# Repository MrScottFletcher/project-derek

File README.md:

# Derek Halloween Animatronic Eyes in a Can System

This repository is for the Derek Halloween Animatronic Eyes in a Can System: a distributed animatronic display built around clusters of moving eyeballs housed in tin cans. The system is designed for synchronized motion, lighting, sound, motion detection, and show control across multiple wireless nodes.

## Project Overview

Each pair of animatronic eyes in a can is called a `Derrick`. A single cluster can control up to eight Derricks, and the full installation can scale to up to 15 cluster nodes coordinated by one Master Control Unit (`MCU`).

Each Derrick includes:

- Two servos
- Addressable RGB LED illumination
- Independent participation in animations and show sequences

The two servos are used for:

- Horizontal eye direction
- Vertical eye lift and conceal/reveal motion

The vertical servo not only raises and lowers the eyes, but also lifts the can lid as the eyes emerge.

## System Architecture

The system is split into two primary firmware roles:

- `MCU` (Master Control Unit)
- `Cluster` controllers

### Master Control Unit

The MCU is the orchestration layer. Its responsibilities include:

- Running or integrating with QLC+ for show control
- Converting OSC-based control intent into cluster commands
- Managing configuration and persistent settings
- Providing a web UI for setup, control, and manual triggering
- Coordinating performances across one or more clusters
- Receiving status updates and PIR motion events from clusters

### Cluster Controllers

Each cluster controller is responsible for local hardware control and fail-safe behavior. A cluster manages:

- Up to eight Derricks
- Servo motion control through a PWM servo controller
- Addressable RGB LED segments for each Derrick
- Two DFPlayer MP3 audio modules
- Audio amplifiers and speakers
- Three PIR motion sensors: left, center, and right
- Wireless communication back to the MCU via ESP-NOW

Clusters should continue operating gracefully even if some hardware subsystems are unavailable, and they should report status back to the MCU whenever possible.

## Control and Communication

The system uses:

- `ESP32`-class controllers
- `ESP-NOW` for wireless MCU-to-cluster communication
- `OSC` and `QLC+` as part of the higher-level control workflow

Communication is bi-directional:

- The MCU sends orchestration, animation, lighting, audio, and motion commands to clusters
- Clusters report status and PIR sensor activity back to the MCU

Wireless message formats should be treated as stable contracts between the MCU and cluster firmware.

## Motion, Lighting, and Audio

### Motion

Each Derrick has:

- One servo for left/right aiming
- One servo for up/down lift and conceal/reveal

Expected motion behavior:

- Straight ahead is centered
- Horizontal movement can sweep left or right within configured limits
- Vertical motion can hide the eyes inside the can or raise them fully into view
- Calibration should support placement of each Derrick within a 360-degree installation layout

Motion control is safety-sensitive and should remain deterministic, non-blocking, and range-clamped.

### Lighting

Each cluster includes addressable RGB LED segments connected in series, with each Derrick owning its own lighting section. Lighting can be used to:

- Illuminate the eyes
- Set mood and scene color
- Synchronize with movement and sound cues

### Audio

Each cluster includes two DFPlayer units, each with an SD card containing an identical numbered MP3 library. Audio can be:

- Triggered per Derrick action
- Triggered by multi-Derrick animations
- Run independently per cluster
- Coordinated across multiple clusters

## Sensing and Reactive Behavior

Each cluster includes three PIR sensors:

- Left
- Center
- Right

These sensors provide motion events that can be sent back to the MCU and used by QLC+ or other orchestration logic to:

- Trigger performances
- Redirect gaze toward detected motion
- Start random or interactive animation sequences

The long-term design also allows for more precise tracking input based on a 360-degree position around the installation.

## Performances and Configuration

The system is intended to support named performances that can span:

- A single Derrick
- A single cluster
- Multiple clusters
- The entire installation

Configurable system concerns include:

- Number of clusters in the installation
- Number of Derricks present in each cluster
- Calibration for each Derrick's motion range and aiming
- Persistent MCU-side settings for orchestration and control

Triggers for performances may include:

- Random timing
- PIR motion input
- Manual operator control through the MCU web interface

## Planned Repository Structure

The repository is expected to organize code by deployable target:

```text
project-derek/
  derek-cluster/
    src/
  derek-mcu/
    src/
```

In this structure:

- `derek-cluster/src/` contains cluster firmware and direct hardware control logic
- `derek-mcu/src/` contains master orchestration, configuration, communications, and web UI logic

## Engineering Guidelines

This project follows a few important design principles:

- Keep MCU and cluster responsibilities clearly separated
- Prefer deterministic, non-blocking runtime behavior
- Avoid changing hardware mappings unless explicitly required
- Preserve graceful degradation when hardware components are unavailable
- Use named constants and configuration structures rather than scattered magic numbers
- Keep serial logging concise and easy to disable
- Make persistent-setting defaults explicit and safe

For embedded code, motion, LEDs, audio, radio, and sensing should be able to operate concurrently without blocking the control loop.

## Development Notes

General project commands:

- Install: `npm install`
- Development: `npm run dev`
- Test: `npm test`
- Lint: `npm run lint`

Additional implementation details may vary between the MCU application and the cluster firmware as those directories are added.

## Current Status

This repository is currently in an early stage and serves as the home for the Derek system architecture, firmware organization, and future control software.

As the codebase grows, this README should be expanded with:

- Build instructions per target
- Hardware BOM and wiring references
- Wireless protocol details
- Calibration workflow
- Performance authoring and deployment notes

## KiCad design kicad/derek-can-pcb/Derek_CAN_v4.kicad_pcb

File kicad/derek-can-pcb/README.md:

# Derek CAN Interface Board Rev 4

This revision adds a schematic and corrects the LED-return net mismatch found in Rev 3.

## Authoritative RJ45 pinout

1. +5 V
2. +5 V
3. GND
4. GND
5. PAN_PWM
6. LIFT_PWM
7. LED_FROM_CLUSTER
8. LED_RETURN_CLUSTER

This is **not Ethernet**. It is intended only for a straight-through 8P8C patch cable connected to the matching Cluster Controller port.

## Components

- C1: 1000 uF, 16 V, radial aluminum electrolytic, 105 C, 5.0 mm lead spacing
- C2: 100 nF, 50 V, X7R radial ceramic, 2.5 mm lead spacing
- R1: 330 ohm axial through-hole resistor

## Schematic format

`Derek_CAN_v4.sch` is a KiCad legacy schematic. Current KiCad versions should open it and offer to convert/save it as `Derek_CAN_v4.kicad_sch`. This was chosen because the legacy format is compact and less prone to hand-generated parser errors.

## Important correction from Rev 3

J5 pin 1 (data from the final LED) and J1 pin 8 (return to the cluster) now share the same net: `LED_RETURN_CLUSTER`.

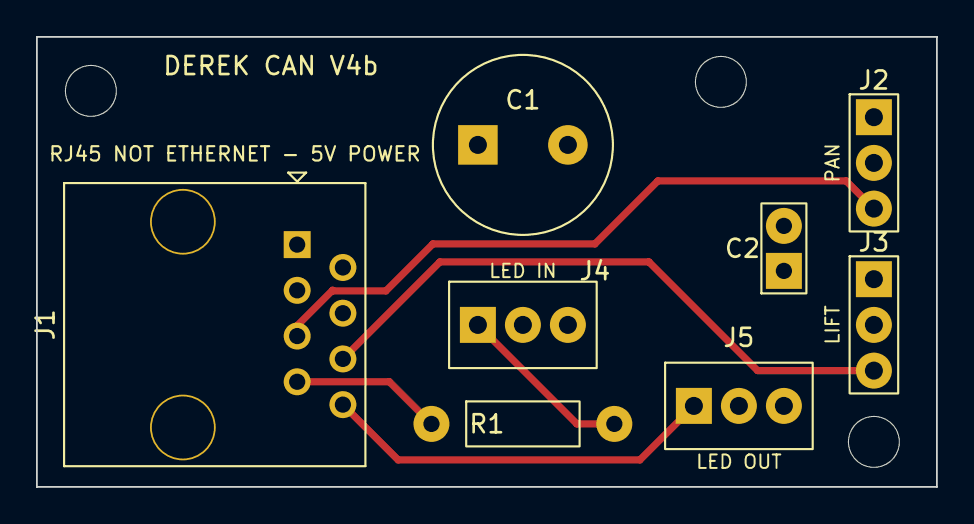
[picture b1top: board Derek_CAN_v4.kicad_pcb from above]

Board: 4 copper layers, 50.0 x 25.0 mm, 8 parts (0 on the bottom side), 7 nets.

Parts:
C1: 1000uF 16V; CP_Radial_D10.0mm_P5.00mm
C2: 100nF 50V X7R; C_Disc_D5.0mm_W2.5mm_P2.50mm
J1: FMHXG_RJ45NMCCFC; RJ45_OST_PJ012-8P8CX_Vertical
J2: PAN_SERVO; PinHeader_1x03_P2.54mm_Vertical
J3: LIFT_SERVO; PinHeader_1x03_P2.54mm_Vertical
J4, J5: JST-XH-3; JST_XH_B3B-XH-A_1x03_P2.50mm_Vertical
R1: 330R; R_Axial_DIN0207_L6.3mm_D2.5mm_P10.16mm_Horizontal

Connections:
5V: C1.1 (+), C2.1, J1.1, J1.2, J2.2 (+5V), J3.2 (+5V), J4.2 (+5V), J5.2 (+5V)
GND: C1.2 (-), C2.2, J1.3, J1.4, J2.1 (GND), J3.1 (GND), J4.3 (GND), J5.3 (GND)
LED_FROM_CLUSTER: J1.7, R1.1
LED_RETURN_CLUSTER: J1.8, J5.1 (DATA)
LED_TO_FIRST: J4.1 (DATA), R1.2
LIFT_PWM: J1.6, J3.3 (SIGNAL)
PAN_PWM: J1.5, J2.3 (SIGNAL)

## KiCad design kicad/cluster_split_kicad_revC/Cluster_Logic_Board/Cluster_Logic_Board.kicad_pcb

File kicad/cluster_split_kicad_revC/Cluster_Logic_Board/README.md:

# Cluster Logic Board Rev G — U1 rebuilt

This revision starts over on U1 rather than translating the bare ESP32-S3 MCU symbol.

## Why this fixes the prior problem

U1 now uses **physical development-board header identifiers** as both schematic pin numbers and PCB pad numbers:

- `J1.1` through `J1.22` = left header
- `J3.1` through `J3.22` = right header

This makes it impossible for KiCad to confuse a DevKit physical header position with a bare ESP32-S3 package pin number.

Key power connections:
- U1 `J1.1` and `J1.2` = 3V3 -> `+3V3_LOGIC`
- U1 `J1.21` = 5V -> `+5V_LOGIC`
- U1 `J1.22`, `J3.1`, `J3.21`, `J3.22` = GND -> `GND`

## GPIO assignments

- GPIO4 = ID0
- GPIO5 = ID1
- GPIO6 = ID2
- GPIO7 = ID3
- GPIO8 = I2C SDA
- GPIO9 = I2C SCL
- GPIO10 = LED data
- GPIO11 = PIR left
- GPIO12 = PIR center
- GPIO13 = PIR right
- GPIO14 = PCA9685 OE
- GPIO15 = ESP TX to DFPlayer #2 RX via R6
- GPIO16 = ESP RX from DFPlayer #2 TX
- GPIO17 = ESP TX to DFPlayer #1 RX via R5
- GPIO18 = ESP RX from DFPlayer #1 TX

## Pins intentionally avoided

- GPIO0, GPIO3, GPIO45, GPIO46: boot/strapping-related
- GPIO19, GPIO20: native USB D-/D+
- GPIO35, GPIO36, GPIO37: avoided for N16R8 / octal PSRAM compatibility
- GPIO43, GPIO44: left free for UART0/programming/debug convenience

## J10 — NOT CHANGED

1. GND
2. GND
3. +3V3_LOGIC
4. I2C_SDA
5. I2C_SCL
6. LED_DATA_3V3
7. PCA_OE_N
8. SPARE

The Cluster Servo Board is not changed by this package.

## Included verification aids

- `U1_Hosyond_Pin_Assignment_Audit.csv`
- `ESP32_Pin_Assignments.h`
- custom U1 footprint under `Halloween.pretty`

Open `Cluster_Logic_Board.kicad_pro` as a KiCad project, then use Update PCB from Schematic. Refill zones and run ERC/DRC before fabrication.

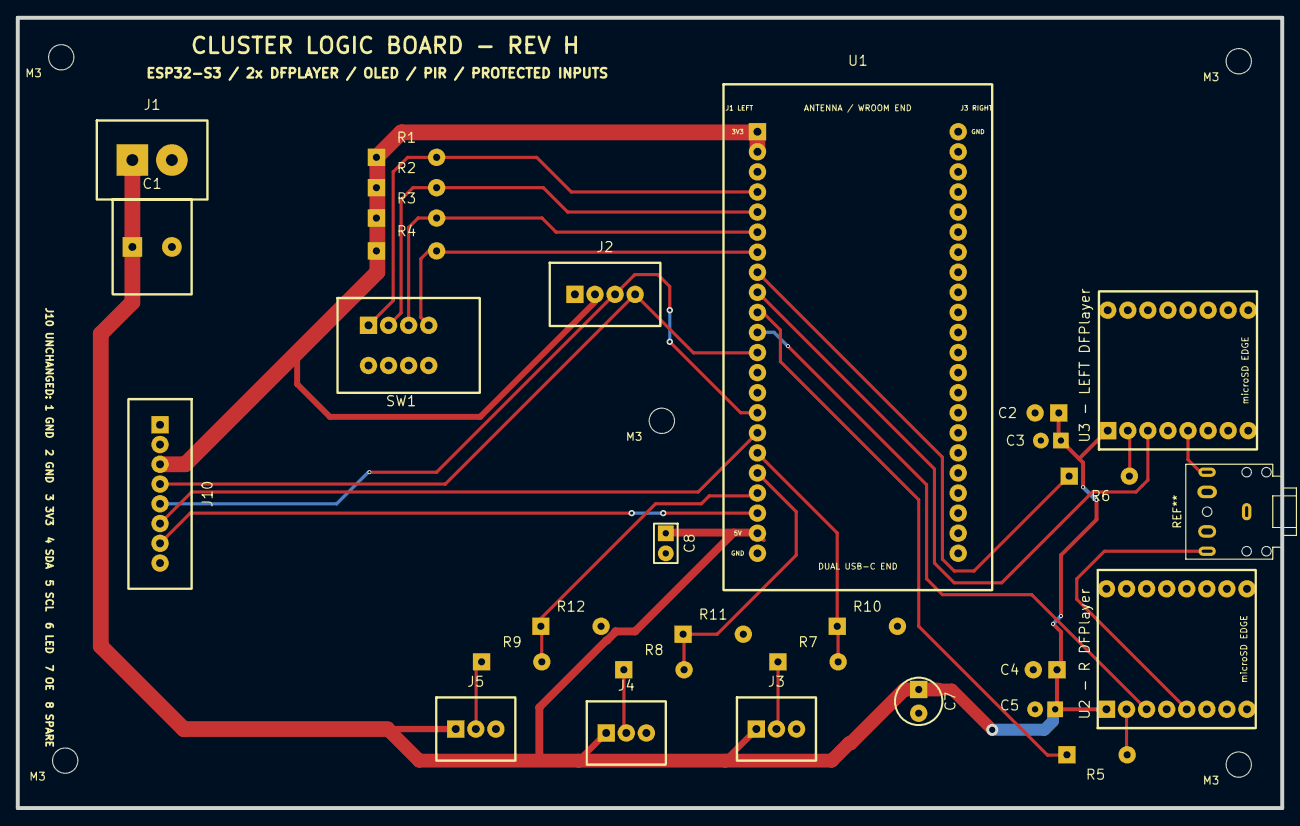
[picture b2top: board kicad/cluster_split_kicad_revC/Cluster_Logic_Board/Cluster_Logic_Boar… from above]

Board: 2 copper layers, 160.0 x 100.0 mm, 34 parts (0 on the bottom side), 23 nets.

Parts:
C1: 1000uF_10V
C2, C4: 47uF 10V; C_Radial_47uF
C3, C5: 100nF; C_Ceramic_100nF
C7: 47uF 10V ESP32; C_Radial_47uF
C8: 100nF ESP32; C_Ceramic_100nF
J1: POWER_5V
J2: OLED_1x4
J3: PIR_LEFT
J4: PIR_CENTER
J5: PIR_RIGHT
J10: JST_XH_8
M3, M3#2, M3#3, M3#4, M3#5: MountingHole_3.2mm_M3
R1, R2, R3, R4: 10k; R_Axial_10k
R5: 1k DF1 RX; R_Axial_1k
R6: 1k DF2 RX; R_Axial_1k
R7: 1k PIR L; R_Axial_1k
R8: 1k PIR C; R_Axial_1k
R9: 1k PIR R; R_Axial_1k
R10, R11, R12: 100k; R_Axial_100k
SW1: DIPSW_4
U1: Hosyond ESP32-S3 N16R8 44-pin DevKit; Hosyond_ESP32-S3_N16R8_44P
U2 - R DFPlayer, U3 - LEFT DFPlayer: WWZMDiB DFPlayer Mini; DFPlayer_Mini_16P

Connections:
+3V3_LOGIC: J2.2, J10.3, R1.1, R2.1, R3.1, R4.1, U1.J1.1, U1.J1.2
+5V_LOGIC: C1.1, C2.1, C3.1, C4.1, C5.1, C7.1, C8.1, J1.1, J3.1, J4.1, J5.1, U1.J1.21, U2 - R DFPlayer.1, U3 - LEFT DFPlayer.1
DF1_RX: R5.2, U2 - R DFPlayer.2
DF1_RX_ESP: R5.1, U1.J1.10
DF1_TX: U1.J1.11, U2 - R DFPlayer.3
DF2_RX: R6.2, U3 - LEFT DFPlayer.2
DF2_RX_ESP: R6.1, U1.J1.8
DF2_TX: U1.J1.9, U3 - LEFT DFPlayer.3
GND: C1.2, C2.2, C3.2, C4.2, C5.2, C7.2, C8.2, J1.2, J2.1, J3.3, J4.3, J5.3, J10.1, J10.2, R10.2, R11.2, R12.2, SW1.5, SW1.6, SW1.7, SW1.8, U1.J1.22, U1.J3.1, U1.J3.21, U1.J3.22, U2 - R DFPlayer.7, U2 - R DFPlayer.10, U3 - LEFT DFPlayer.7, U3 - LEFT DFPlayer.10
I2C_SCL: J2.3, J10.5, U1.J1.15
I2C_SDA: J2.4, J10.4, U1.J1.12
ID0: R1.2, SW1.1, U1.J1.4
ID1: R2.2, SW1.2, U1.J1.5
ID2: R3.2, SW1.3, U1.J1.6
ID3: R4.2, SW1.4, U1.J1.7
LED_DATA_3V3: J10.6, U1.J1.16
PCA_OE_N: J10.7, U1.J1.20
PIR_CENTER: R8.2, R11.1, U1.J1.18
PIR_CENTER_CONN: J4.2, R8.1
PIR_LEFT: R7.2, R10.1, U1.J1.17
PIR_LEFT_CONN: J3.2, R7.1
PIR_RIGHT: R9.2, R12.1, U1.J1.19
PIR_RIGHT_CONN: J5.2, R9.1

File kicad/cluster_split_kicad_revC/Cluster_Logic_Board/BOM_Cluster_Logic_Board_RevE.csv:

Reference,Qty,Part / Value,Footprint,Assembly,Purpose / placement
U1,1,Hosyond ESP32-S3 N16R8 Dev Board,Existing 2x22 carrier footprint,Hand,Controller module
"U2,U3",2,WWZMDiB DFPlayer Mini compatible,Halloween:DFPlayer_Mini_16P,Hand,Audio modules
J2,1,"0.96in SSD1306 I2C OLED, GND/VCC/SCL/SDA",Halloween:OLED_SSD1306_096_4P,Hand,Display
"J3,J4,J5",3,PIR 3-pin headers,2.54mm THT,Hand,PIR sensors
SW1,1,4-position DIP switch,DIP-8 W7.62mm,Hand,Cluster ID
J10,1,JST-XH 1x8 2.50mm,JST_XH_B8B-XH-A,Hand,UNCHANGED servo-board interconnect
R1-R4,4,10k 1/4W axial,DIN0207 axial THT,Hand,SW1 ID pull-ups to 3.3V
R5-R6,2,1k 1/4W axial,DIN0207 axial THT,Hand,ESP32 TX -> DFPlayer RX
R7-R9,3,1k 1/4W axial,DIN0207 axial THT,Hand,PIR signal series protection
R10-R12,3,100k 1/4W axial,DIN0207 axial THT,Hand,PIR input pulldowns
C1,1,1000uF 10V radial electrolytic,CP_Radial_D10mm_P5mm,Hand,Main logic-board bulk at J1
"C2,C4",2,47uF 10V radial electrolytic,CP_Radial_D5mm_P2mm,Hand,One near each DFPlayer
"C3,C5",2,100nF ceramic,C_Disc_D5mm_P5mm,Hand,One near each DFPlayer
C6,1,100nF ceramic,C_Disc_D5mm_P5mm,Hand,PIR connector-bank bypass
C7,1,47uF 10V radial electrolytic,CP_Radial_D5mm_P2mm,Hand,Local bulk near ESP32 5V/VIN
C8,1,100nF ceramic,C_Disc_D5mm_P5mm,Hand,Local high-frequency bypass near ESP32 5V/VIN

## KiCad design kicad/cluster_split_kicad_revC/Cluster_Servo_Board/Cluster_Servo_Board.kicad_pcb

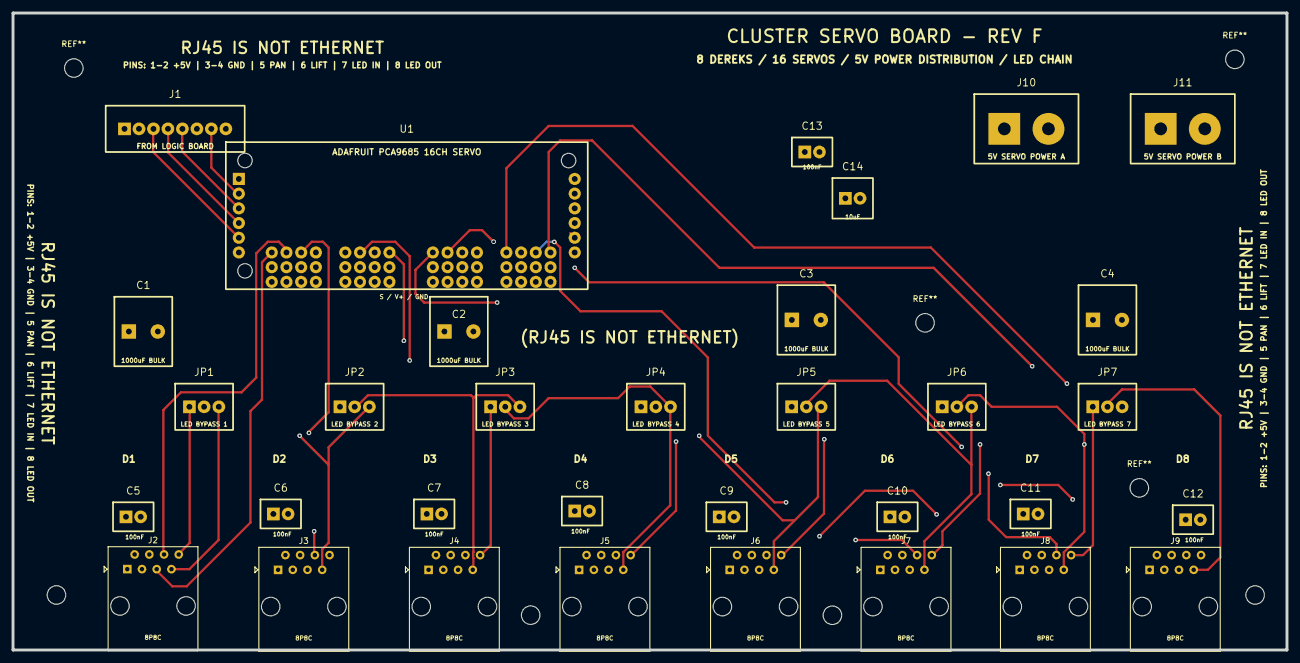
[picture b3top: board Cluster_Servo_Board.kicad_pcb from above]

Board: 4 copper layers, 220.0 x 110.0 mm, 33 parts (0 on the bottom side), 37 nets.

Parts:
C1, C2, C3, C4: 1000uF_10V
C5, C6, C7, C8, C9, C10, C11, C12, C13: 100nF
C14: 10uF
J1: JST_XH_8
J2, J3, J4, J5, J6, J7, J8, J9: RJ45_Amphenol_54602-x08_Horizontal
J10, J11: POWER_5V_HICUR
JP1, JP2, JP3, JP4, JP5, JP6, JP7: LED_BYPASS
U1: ADAFRUIT_PCA9685_16CH_PRODUCT_815; Adafruit_PCA9685_16CH_Product815_Carrier

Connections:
+3V3_LOGIC: J1.3, U1.L5, U1.R5
+5V_SERVO: C1.1, C2.1, C3.1, C4.1, C5.1, C6.1, C7.1, C8.1, C9.1, C10.1, C11.1, C12.1, C13.1, C14.1, J2.1, J2.2, J3.1, J3.2, J4.1, J4.2, J5.1, J5.2, J6.1, J6.2, J7.1, J7.2, J8.1, J8.2, J9.1, J9.2, J10.1, J11.1, U1.L6, U1.R6, U1.V0, U1.V1, U1.V2, U1.V3, U1.V4, U1.V5, U1.V6, U1.V7, U1.V8, U1.V9, U1.V10, U1.V11, U1.V12, U1.V13, U1.V14, U1.V15
GND: C1.2, C2.2, C3.2, C4.2, C5.2, C6.2, C7.2, C8.2, C9.2, C10.2, C11.2, C12.2, C13.2, C14.2, J1.1, J1.2, J2.3, J2.4, J3.3, J3.4, J4.3, J4.4, J5.3, J5.4, J6.3, J6.4, J7.3, J7.4, J8.3, J8.4, J9.3, J9.4, J10.2, J11.2, U1.G0, U1.G1, U1.G2, U1.G3, U1.G4, U1.G5, U1.G6, U1.G7, U1.G8, U1.G9, U1.G10, U1.G11, U1.G12, U1.G13, U1.G14, U1.G15, U1.L1, U1.R1
I2C_SCL: J1.5, U1.L3, U1.R3
I2C_SDA: J1.4, U1.L4, U1.R4
LED_IN1: J2.7, JP1.3
LED_IN2: J3.7, JP1.2, JP2.3
LED_IN3: J4.7, JP2.2, JP3.3
LED_IN4: J5.7, JP3.2, JP4.3
LED_IN5: J6.7, JP4.2, JP5.3
LED_IN6: J7.7, JP5.2, JP6.3
LED_IN7: J8.7, JP6.2, JP7.3
LED_IN8: J9.7, JP7.2
LED_OUT1: J2.8, JP1.1
LED_OUT2: J3.8, JP2.1
LED_OUT3: J4.8, JP3.1
LED_OUT4: J5.8, JP4.1
LED_OUT5: J6.8, JP5.1
LED_OUT6: J7.8, JP6.1
LED_OUT7: J8.8, JP7.1
PCA_OE_N: J1.7, U1.L2, U1.R2
PWM0: J2.5, U1.S0
PWM1: J2.6, U1.S1
PWM2: J3.5, U1.S2
PWM3: J3.6, U1.S3
PWM4: J4.5, U1.S4
PWM5: J4.6, U1.S5
PWM6: J5.5, U1.S6
PWM7: J5.6, U1.S7
PWM8: J6.5, U1.S8
PWM9: J6.6, U1.S9
PWM10: J7.5, U1.S10
PWM11: J7.6, U1.S11
PWM12: J8.5, U1.S12
PWM13: J8.6, U1.S13
PWM14: J9.5, U1.S14
PWM15: J9.6, U1.S15

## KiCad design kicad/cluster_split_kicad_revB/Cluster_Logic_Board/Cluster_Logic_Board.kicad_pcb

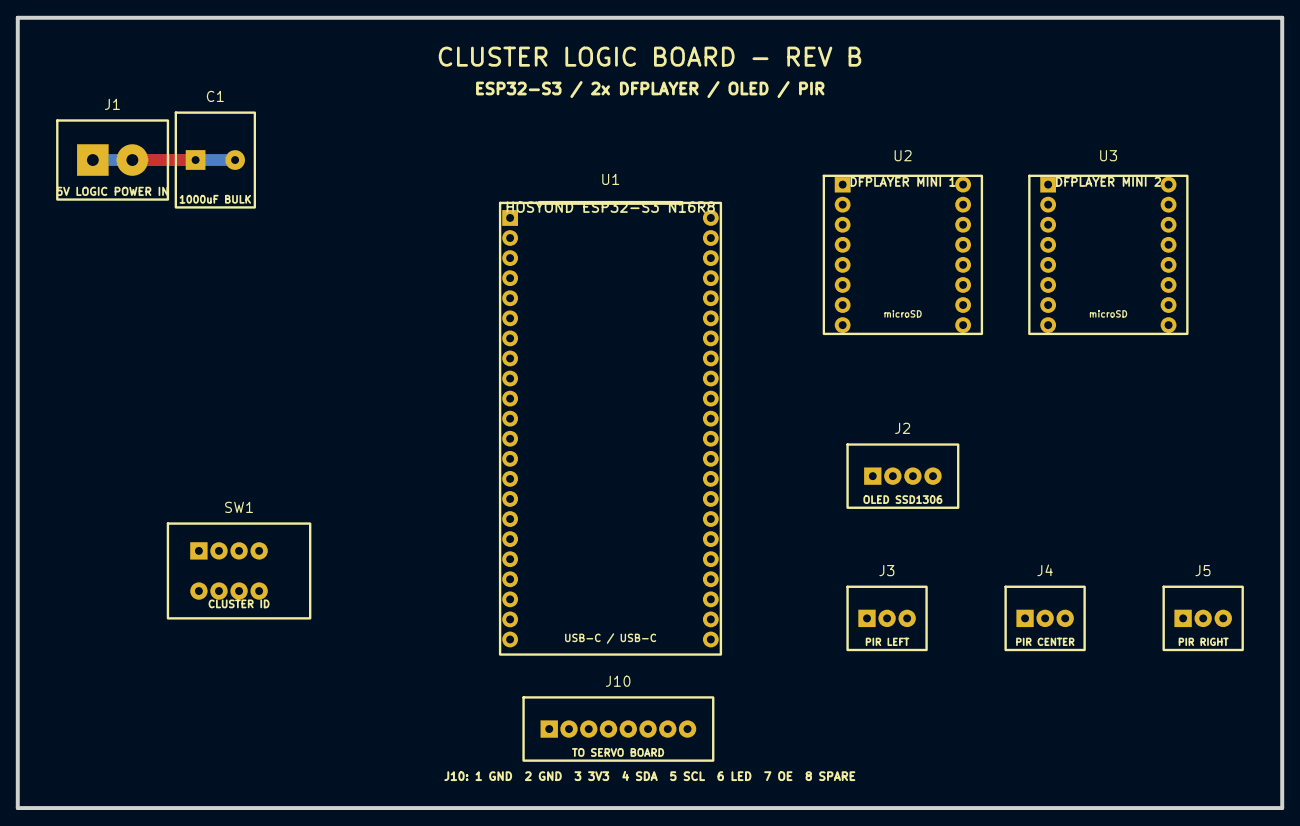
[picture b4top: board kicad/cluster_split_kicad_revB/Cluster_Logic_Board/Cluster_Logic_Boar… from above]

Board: 2 copper layers, 160.0 x 100.0 mm, 11 parts (0 on the bottom side), 18 nets.

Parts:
C1: 1000uF_10V
J1: POWER_5V
J2: OLED_1x4
J3: PIR_LEFT
J4: PIR_CENTER
J5: PIR_RIGHT
J10: JST_XH_8
SW1: DIPSW_4
U1: HOSYOND_ESP32-S3_N16R8_2x22; ESP32_S3_HOSYOND_N16R8_2x22_WIDE
U2: DFPLAYER_MINI_1; DFPlayer_Mini_16P_20x20mm
U3: DFPLAYER_MINI_2; DFPlayer_Mini_16P_20x20mm

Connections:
+3V3_LOGIC: J2.2, J10.3, U1.3
+5V_LOGIC: C1.1, J1.1, J3.1, J4.1, J5.1, U1.1, U2.1, U3.1
DF1_RX: U1.9, U2.2
DF1_TX: U1.8, U2.3
DF2_RX: U1.11, U3.2
DF2_TX: U1.10, U3.3
GND: C1.2, J1.2, J2.1, J3.3, J4.3, J5.3, J10.1, J10.2, SW1.5, SW1.6, SW1.7, SW1.8, U1.2, U2.7, U2.10, U3.7, U3.10
I2C_SCL: J2.3, J10.5, U1.5
I2C_SDA: J2.4, J10.4, U1.4
ID0: SW1.1, U1.15
ID1: SW1.2, U1.16
ID2: SW1.3, U1.17
ID3: SW1.4, U1.18
LED_DATA_3V3: J10.6, U1.6
PCA_OE_N: J10.7, U1.7
PIR_CENTER: J4.2, U1.13
PIR_LEFT: J3.2, U1.12
PIR_RIGHT: J5.2, U1.14

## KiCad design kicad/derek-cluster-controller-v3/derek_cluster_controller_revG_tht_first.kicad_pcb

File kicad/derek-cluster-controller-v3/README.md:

# Derek Cluster Controller Rev D - 220 x 220 mm, 6-layer, clean placement

This is a fresh KiCad starter derived from the Rev C concept, with the focus requested:

1. More component-specific footprints rather than generic blocks.
2. Power distribution intended to support portions of a 15A total 5V budget to the RJ45 Derek connectors.
3. No deliberate component overlaps.
4. Initial trace routing and power-plane structure.

## Important limitations
This is still a starter project, not a finished PCB. It does not replace a real KiCad ERC/DRC workflow. The ESP32-S3, Adafruit PCA9685, DFPlayer Mini, OLED, and especially RJ45 clone footprints MUST be verified with a 1:1 printout against the exact physical parts before sending to PCBWay.

## Board
- Size: 220 mm x 220 mm
- 6 layers:
  - F.Cu: components / primary signals / local high-current bus
  - In1.Cu: GND plane
  - In2.Cu: protected 5V plane
  - In3.Cu: signal layer
  - In4.Cu: secondary GND/stitch plane
  - B.Cu: secondary signals

## Power distribution
- 5V input -> fuse -> PMOS reverse protection -> 5V_PROT
- L3/In2.Cu is the main protected 5V plane.
- F.Cu includes a bottom high-current 5V distribution zone near the RJ45 row.
- There are multiple 5V vias around the RJ45 bank to couple the F.Cu bus to the L3 5V plane.
- L2 and L5 are GND planes.
- Bulk capacitance: 4700uF input, 1000uF RJ45 bank, four 100uF local zone caps.

## RJ45 row
All eight RJ45 Derek jacks are placed in a single bottom-edge row for cable access. Pinout:
1 +5V
2 +5V
3 GND
4 GND
5 Pan PWM
6 Lift PWM
7 LED Data In
8 LED Data Out

## Component-specific updates
- DFPlayer Mini: 20mm x 20mm, 16-pin dual-row standard module footprint, SD access toward right edge.
- OLED: 0.96in SSD1306 I2C 128x64 27mm x 27mm 4-pin GND/VCC/SCL/SDA footprint, powered from 3.3V.
- RJ45: FMHXG RJ45NMCCFC-90D approximate right-angle jack footprint.
- PCA9685: Adafruit 815 carrier-style footprint approximation.

## Before PCBWay
1. Print PCB at 1:1 scale.
2. Place every actual part on the printout.
3. Check RJ45 jack pin/post alignment.
4. Check DFPlayer SD card removal clearance.
5. Check ESP32 USB cable access and antenna keepout.
6. Run KiCad DRC.
7. Fill zones and inspect power-plane connectivity.
8. Export Gerbers and review in PCBWay viewer before ordering.

## Rev D schematic-added note
The original Rev D schematic was blank. This package replaces it with a visible architectural schematic sheet documenting the intended modules, power nets, RJ45 pinout, LED daisy chain, and control nets. It is still not a complete ERC-clean production schematic; verify exact symbols/footprints before fabrication.

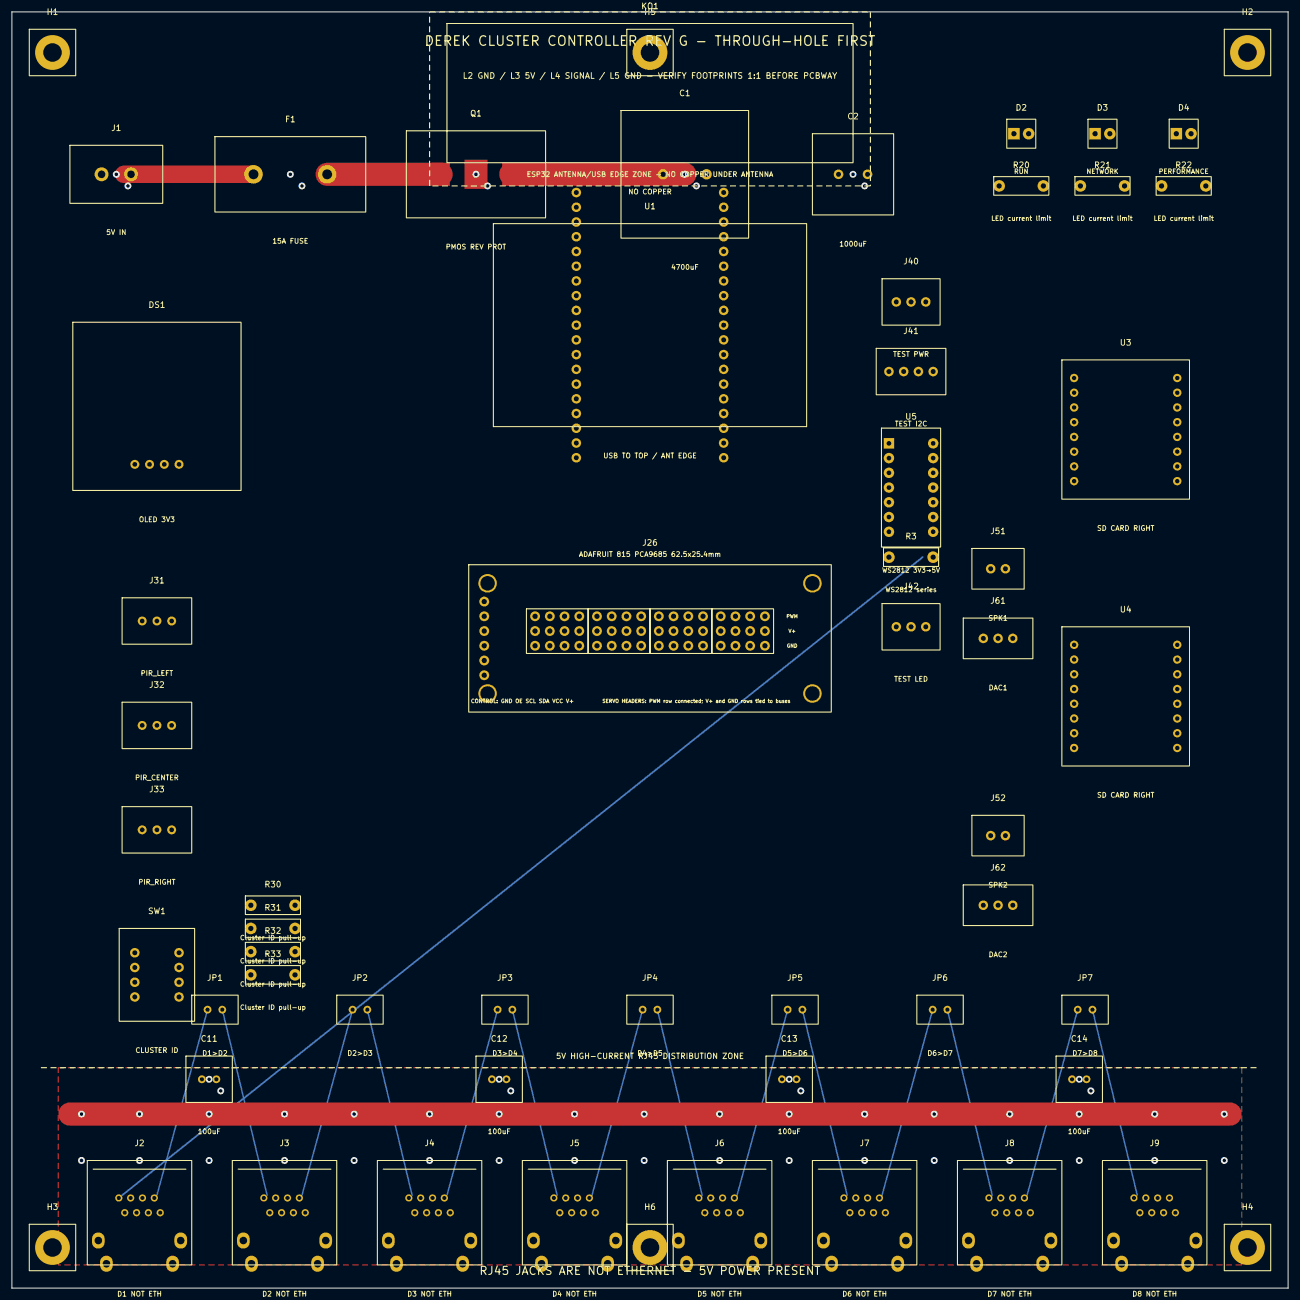
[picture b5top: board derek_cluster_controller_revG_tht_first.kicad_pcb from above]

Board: 6 copper layers, 220.0 x 220.0 mm, 59 parts (0 on the bottom side), 64 nets.

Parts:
C1: RADIAL_ECAP_4700uF_10V_D18_P7.5
C2: RADIAL_ECAP_1000uF_10V_D10_P5
C11, C12, C13, C14: RADIAL_ECAP_100uF_10V_D6_P2p5_RJ45_PAIR
D2, D3, D4: LED 3mm THT; LED_D3.0mm
DS1: SSD1306_OLED_0p96_128x64_I2C_27x27_4PIN_GND_VCC_S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; SSD1306_OLED_0p96_128x64_I2C_27x27_4PIN_GND_VCC_SCL_SDA
F1: KEYSTONE_3568_ATO_ATC_BLADE_FUSE_15A
H1, H2, H3, H4, H5, H6: M3_MOUNT_HOLE_PLATED_GND
J1: XY301V_5.08_2P_5V_INPUT_15A
J2, J3, J4, J5, J6, J7, J8, J9: FMHXG_RJ45NMCCFC_90D_RIGHT_ANGLE_8P8C_APPROX_VERI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; FMHXG_RJ45NMCCFC_90D_RIGHT_ANGLE_8P8C_APPROX_VERIFY
J26: Adafruit Product 815 PCA9685 Breakout Socket; Adafruit_815_PCA9685_Breakout_CarrierSocket_VERIFY
J31: JST_XH_3PIN_PIR_LEFT
J32: JST_XH_3PIN_PIR_CENTER
J33: JST_XH_3PIN_PIR_RIGHT
J40: TEST_POWER_3PIN
J41: TEST_I2C_4PIN
J42: TEST_LED_3PIN
J51: DF1_SPEAKER_2PIN
J52: DF2_SPEAKER_2PIN
J61: DF1_DAC_LR_GND_3PIN
J62: DF2_DAC_LR_GND_3PIN
JP1: LED_CHAIN_JUMPER_D1_TO_D2_2PIN
JP2: LED_CHAIN_JUMPER_D2_TO_D3_2PIN
JP3: LED_CHAIN_JUMPER_D3_TO_D4_2PIN
JP4: LED_CHAIN_JUMPER_D4_TO_D5_2PIN
JP5: LED_CHAIN_JUMPER_D5_TO_D6_2PIN
JP6: LED_CHAIN_JUMPER_D6_TO_D7_2PIN
JP7: LED_CHAIN_JUMPER_D7_TO_D8_2PIN
KO1: ESP32_ANTENNA_KEEP_OUT_70x24_NO_COPPER
Q1: D2PAK_PMOS_REVERSE_PROTECTION_VERIFY_FQP27P06_OR_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; D2PAK_PMOS_REVERSE_PROTECTION_VERIFY_FQP27P06_OR_EQUIV
R3: 330Ω 1/4W; R_Axial_DIN0207_L6.3_D2.5_P7.62
R20, R21, R22: 1kΩ 1/4W; R_Axial_DIN0207_L6.3_D2.5_P7.62
R30, R31, R32, R33: 10kΩ 1/4W; R_Axial_DIN0207_L6.3_D2.5_P7.62
SW1: DIP_SWITCH_4_SPST_2p54_CLUSTER_ID
U1: ESP32_S3_DEVKITC_1_SOCKET_2x19_2p54_VERIFY
U3: DFPLAYER_MINI_STANDARD_20x20_16PIN_SD_RIGHT_DF1
U4: DFPLAYER_MINI_STANDARD_20x20_16PIN_SD_RIGHT_DF2
U5: SN74AHCT125N DIP-14; DIP-14_W7.62mm_SN74AHCT125N

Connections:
3V3: D2.1 (A), D3.1 (A), D4.1 (A), DS1.2 (VCC), J26.5 (VCC), J40.2 (3V3), J41.1 (3V3), R30.1, R31.1, R32.1, R33.1, U1.1 (3V3)
5V_IN: F1.1 (IN), J1.1 (+5V), Q1.3 (SOURCE)
5V_PROT: C1.1 (+), C2.1 (+), C11.1 (+), C12.1 (+), C13.1 (+), C14.1 (+), F1.2 (OUT), J2.1, J2.2, J3.1, J3.2, J4.1, J4.2, J5.1, J5.2, J6.1, J6.2, J7.1, J7.2, J8.1, J8.2, J9.1, J9.2, J26.6 (V+), J26.V0 (CH0_VPLUS), J26.V1 (CH1_VPLUS), J26.V2 (CH2_VPLUS), J26.V3 (CH3_VPLUS), J26.V4 (CH4_VPLUS), J26.V5 (CH5_VPLUS), J26.V6 (CH6_VPLUS), J26.V7 (CH7_VPLUS), J26.V8 (CH8_VPLUS), J26.V9 (CH9_VPLUS), J26.V10 (CH10_VPLUS), J26.V11 (CH11_VPLUS), J26.V12 (CH12_VPLUS), J26.V13 (CH13_VPLUS), J26.V14 (CH14_VPLUS), J26.V15 (CH15_VPLUS), J31.1 (5V), J32.1 (5V), J33.1 (5V), J40.1 (5V), J42.1 (5V), Q1.2 (DRAIN), U1.1 (5V/VIN), U3.1 (VCC), U3.16 (VCC), U4.1 (VCC), U4.16 (VCC), U5.4 (~OE2), U5.10 (~OE3), U5.13 (~OE4), U5.14 (VCC)
D1_LED_IN: J2.7, J42.2 (DATA), R3.2
D1_LED_OUT: J2.8, JP1.1 (OUT)
D1_LIFT: J2.6, J26.11 (CH1_PWM)
D1_PAN: J2.5, J26.10 (CH0_PWM)
D2_LED_IN: J3.7, JP1.2 (IN)
D2_LED_OUT: J3.8, JP2.1 (OUT)
D2_LIFT: J3.6, J26.13 (CH3_PWM)
D2_PAN: J3.5, J26.12 (CH2_PWM)
D3_LED_IN: J4.7, JP2.2 (IN)
D3_LED_OUT: J4.8, JP3.1 (OUT)
D3_LIFT: J4.6, J26.15 (CH5_PWM)
D3_PAN: J4.5, J26.14 (CH4_PWM)
D4_LED_IN: J5.7, JP3.2 (IN)
D4_LED_OUT: J5.8, JP4.1 (OUT)
D4_LIFT: J5.6, J26.17 (CH7_PWM)
D4_PAN: J5.5, J26.16 (CH6_PWM)
D5_LED_IN: J6.7, JP4.2 (IN)
D5_LED_OUT: J6.8, JP5.1 (OUT)
D5_LIFT: J6.6, J26.19 (CH9_PWM)
D5_PAN: J6.5, J26.18 (CH8_PWM)
D6_LED_IN: J7.7, JP5.2 (IN)
D6_LED_OUT: J7.8, JP6.1 (OUT)
D6_LIFT: J7.6, J26.21 (CH11_PWM)
D6_PAN: J7.5, J26.20 (CH10_PWM)
D7_LED_IN: J8.7, JP6.2 (IN)
D7_LED_OUT: J8.8, JP7.1 (OUT)
D7_LIFT: J8.6, J26.23 (CH13_PWM)
D7_PAN: J8.5, J26.22 (CH12_PWM)
D8_LED_IN: J9.7, JP7.2 (IN)
D8_LIFT: J9.6, J26.25 (CH15_PWM)
D8_PAN: J9.5, J26.24 (CH14_PWM)
DAC1_L: J61.1 (L), U3.6 (DAC_L)
DAC1_R: J61.2 (R), U3.5 (DAC_R)
DAC2_L: J62.1 (L), U4.6 (DAC_L)
DAC2_R: J62.2 (R), U4.5 (DAC_R)
DF1_BUSY: U1.5 (GPIO15), U3.4 (BUSY)
DF1_RX: U1.3 (GPIO17_TX1), U3.2 (RX)
DF1_TX: U1.4 (GPIO18_RX1), U3.3 (TX)
DF2_BUSY: U1.8 (GPIO47), U4.4 (BUSY)
DF2_RX: U1.6 (GPIO16_TX2), U4.2 (RX)
DF2_TX: U1.7 (GPIO21_RX2), U4.3 (TX)
GND: C1.2 (-), C2.2 (-), C11.2 (-), C12.2 (-), C13.2 (-), C14.2 (-), DS1.1 (GND), H1.1 (MOUNT), H2.1 (MOUNT), H3.1 (MOUNT), H4.1 (MOUNT), H5.1 (MOUNT), H6.1 (MOUNT), J1.2 (GND), J2.3, J2.4, J2.M1 (SHIELD), J2.M2 (SHIELD), J2.S1 (SHIELD), J2.S2 (SHIELD), J3.3, J3.4, J3.M1 (SHIELD), J3.M2 (SHIELD), J3.S1 (SHIELD), J3.S2 (SHIELD), J4.3, J4.4, J4.M1 (SHIELD), J4.M2 (SHIELD), J4.S1 (SHIELD), J4.S2 (SHIELD), J5.3, J5.4, J5.M1 (SHIELD), J5.M2 (SHIELD), J5.S1 (SHIELD), J5.S2 (SHIELD), J6.3, J6.4, J6.M1 (SHIELD), J6.M2 (SHIELD), J6.S1 (SHIELD), J6.S2 (SHIELD), J7.3, J7.4, J7.M1 (SHIELD), J7.M2 (SHIELD), J7.S1 (SHIELD), J7.S2 (SHIELD), J8.3, J8.4, J8.M1 (SHIELD), J8.M2 (SHIELD), J8.S1 (SHIELD), J8.S2 (SHIELD), J9.3, J9.4, J9.M1 (SHIELD), J9.M2 (SHIELD), J9.S1 (SHIELD), J9.S2 (SHIELD), J26.1 (GND), J26.G0 (CH0_GND), J26.G1 (CH1_GND), J26.G2 (CH2_GND), J26.G3 (CH3_GND), J26.G4 (CH4_GND), J26.G5 (CH5_GND), J26.G6 (CH6_GND), J26.G7 (CH7_GND), J26.G8 (CH8_GND), J26.G9 (CH9_GND), J26.G10 (CH10_GND), J26.G11 (CH11_GND), J26.G12 (CH12_GND), J26.G13 (CH13_GND), J26.G14 (CH14_GND), J26.G15 (CH15_GND), J31.3 (GND), J32.3 (GND), J33.3 (GND), J40.3 (GND), J41.4 (GND), J42.3 (GND), J61.3 (GND), J62.3 (GND), Q1.1 (GATE), R20.2, R21.2, R22.2, SW1.5 (GND), SW1.6 (GND), SW1.7 (GND), SW1.8 (GND), U1.2 (GND), U1.19 (GND), U3.7 (GND), U3.8 (GND), U3.11 (GND), U4.7 (GND), U4.8 (GND), U4.11 (GND), U5.1 (~OE1), U5.5 (2A), U5.7 (GND), U5.9 (3A), U5.12 (4A)
I2C_SCL: DS1.3 (SCL), J26.3 (SCL), J41.3 (SCL), U1.8 (GPIO9)
I2C_SDA: DS1.4 (SDA), J26.4 (SDA), J41.2 (SDA), U1.7 (GPIO8)
ID0: R30.2, SW1.1 (ID0), U1.3 (GPIO4)
ID1: R31.2, SW1.2 (ID1), U1.4 (GPIO5)
ID2: R32.2, SW1.3 (ID2), U1.5 (GPIO6)
ID3: R33.2, SW1.4 (ID3), U1.6 (GPIO7)
LED_5V: R3.1, U5.3 (1Y)
LED_RAW: U1.9 (GPIO10), U5.2 (1A)
NET_LED: D3.2 (K), R21.1
PCA_OE: J26.2 (OE), U1.13 (GPIO14)
PERF_LED: D4.2 (K), R22.1
PIR_CENTER: J32.2 (SIG), U1.11 (GPIO12)
PIR_LEFT: J31.2 (SIG), U1.10 (GPIO11)
PIR_RIGHT: J33.2 (SIG), U1.12 (GPIO13)
RUN_LED: D2.2 (K), R20.1
SPK1A: J51.1 (SPK+), U3.9 (SPK1)
SPK1B: J51.2 (SPK-), U3.10 (SPK2)
SPK2A: J52.1 (SPK+), U4.9 (SPK1)
SPK2B: J52.2 (SPK-), U4.10 (SPK2)

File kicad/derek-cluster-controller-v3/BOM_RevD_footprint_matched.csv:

Ref,Qty,Footprint/component assumption,Suggested part / buy description,Notes
PCB,1,220x220mm 6-layer FR-4,"PCBWay 6-layer, 1.6mm, 1oz outer/inner or heavier if budget allows","L2/L5 GND, L3 5V."
J1,1,2-pin 5.08mm high-current screw terminal,XY301V/ KF301-5.08-2P or equivalent rated >=15A,Verify current rating; many cheap 5.08 terminals are not 15A.
F1,1,ATO/ATC blade fuse holder,Keystone 3568 or equivalent PCB blade fuse holder,Use 15A fuse.
Q1,1,D2PAK/TO-263 P-channel MOSFET reverse protection,"P-channel MOSFET >=30V, low Rds(on), >=30A; verify pinout",Footprint must match chosen MOSFET.
C1,1,"Radial electrolytic 18mm dia, 7.5mm pitch",4700uF 10V or 16V low-ESR electrolytic,Input bulk.
C2,1,"Radial electrolytic 10mm dia, 5mm pitch",1000uF 10V or 16V electrolytic,RJ45 bank bulk.
C11-C14,4,"Radial electrolytic 6mm dia, 2.5mm pitch",100uF 10V or 16V electrolytic,One per two RJ45 ports.
U1,1,ESP32-S3 DevKitC-1 style 2x19 2.54mm socket,ESP32-S3-DevKitC-1 or matching module,MUST verify exact pin count/header spacing against your module.
J26,1,Adafruit 815 PCA9685 carrier footprint approximation,Adafruit 16-Channel 12-bit PWM/Servo Driver Product 815,Footprint is carrier-style; print 1:1 and verify.
"U3,U4",2,DFPlayer Mini standard 20x20mm 16-pin module,DFRobot DFR0299 / common DFPlayer Mini module,SD card faces right edge. Pinouts vary by clone; verify labels.
DS1,1,0.96in SSD1306 27x27mm 4-pin GND/VCC/SCL/SDA,0.96 Inch OLED I2C 128x64 SSD1306 module,Powered from 3.3V. Verify pin order.
J2-J9,8,FMHXG RJ45NMCCFC-90D approximate right-angle RJ45,FMHXG RJ45NMCCFC-90D 90 degree PCB RJ45 jack,MUST print 1:1 and test-fit actual jack.
U5,1,74AHCT125 level shifter,SN74AHCT125N or SMD equivalent,VCC=5V for WS2812 data.
SW1,1,4-position DIP switch 2.54mm,Generic 4P SPST DIP switch,Cluster ID.
R30-R33,4,0805 resistor,10k 0805,DIP pullups.
R3,1,0805 resistor,330 ohm 0805,WS2812 series resistor.
D2-D4,3,0805 LED,0805 indicator LED,Status indicators.
R20-R22,3,0805 resistor,1k 0805,LED series resistors.
J31-J33,3,JST-XH 3-pin,JST-XH 2.54mm 3-pin headers,PIR connectors.
JP1-JP7,7,2-pin 2.54mm jumper,2-pin header + shunt,LED chain continuation jumpers.
"J51,J52",2,2-pin header/screw terminal,Speaker output connector,For DFPlayer speaker outputs.
"J61,J62",2,3-pin header,DAC L/R/GND output connector,For optional external amp.
H1-H6,6,M3 plated mounting hole,M3 screw + standoff,Grounded mounting holes.

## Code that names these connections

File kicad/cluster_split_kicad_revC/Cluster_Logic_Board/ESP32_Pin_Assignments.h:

#pragma once
// Cluster Logic Board Rev G - Hosyond ESP32-S3 N16R8
// GPIO numbers are Arduino GPIO numbers, not physical carrier header positions.

constexpr int PIN_ID0 = 4;
constexpr int PIN_ID1 = 5;
constexpr int PIN_ID2 = 6;
constexpr int PIN_ID3 = 7;

constexpr int PIN_I2C_SDA = 8;
constexpr int PIN_I2C_SCL = 9;
constexpr int PIN_LED_DATA = 10;

constexpr int PIN_PIR_LEFT   = 11;
constexpr int PIN_PIR_CENTER = 12;
constexpr int PIN_PIR_RIGHT  = 13;
constexpr int PIN_PCA_OE_N   = 14;

constexpr int PIN_DF2_TX = 15;  // ESP TX -> R6 -> DFPlayer #2 RX
constexpr int PIN_DF2_RX = 16;  // DFPlayer #2 TX -> ESP RX
constexpr int PIN_DF1_TX = 17;  // ESP TX -> R5 -> DFPlayer #1 RX
constexpr int PIN_DF1_RX = 18;  // DFPlayer #1 TX -> ESP RX

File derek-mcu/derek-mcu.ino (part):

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constexpr char kWifiPassword[] = "derekderek";

// MCU OLED: Hosyond 2.42-inch 128x64 I2C module with an SSD1309 controller.
// Wiring on this board: GND, VCC, SCL -> GPIO9, SDA/SCA -> GPIO8.
// Test inputs use internal pull-ups: wire each switch/button from its GPIO to GND.
// GPIO4: test-mode switch; GPIO5: All Up button; GPIO6: All Down button.
constexpr int8_t kButtonNextPin = -1;
constexpr int8_t kButtonPrevPin = -1;

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  char line[22] = {};
  writeOledLine(0, "MCU TEST MODE");
  writeOledLine(1, gTestLiftState == kTestLiftAllUp ? "INTENDED ALL UP" : "INTENDED ALL DOWN");
  writeOledLine(2, "GPIO5 ALL UP");
  writeOledLine(3, "GPIO6 ALL DOWN");
  snprintf(line, sizeof(line), "NODES %u ONLINE %u", countRegisteredClusters(), countOnlineClusters());
  writeOledLine(4, line);
  writeOledLine(5, "ARTNET INPUT PAUSED");
  writeOledLine(6, "ESP-NOW ACTIVE");
  writeOledLine(7, "SWITCH GPIO4 ON");
}

uint8_t dmxToPan(uint8_t value) {
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  }

  writeOledTestModePage();
  Serial.println("MCU test mode enabled: Art-Net input paused; GPIO5=All Up, GPIO6=All Down.");
}

void initializeRemoteInputs() {
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
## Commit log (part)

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2026-05-30 Expand project README
2026-05-30 Added AGENTS.md file with project info and some Arduino directives.
2026-05-30 Some tweaks to the AGENTS file
2026-05-30 small tweak to the MCU description
2026-05-30 Initial Codex version based on the Agents.md file. Untested, not reviewed.
